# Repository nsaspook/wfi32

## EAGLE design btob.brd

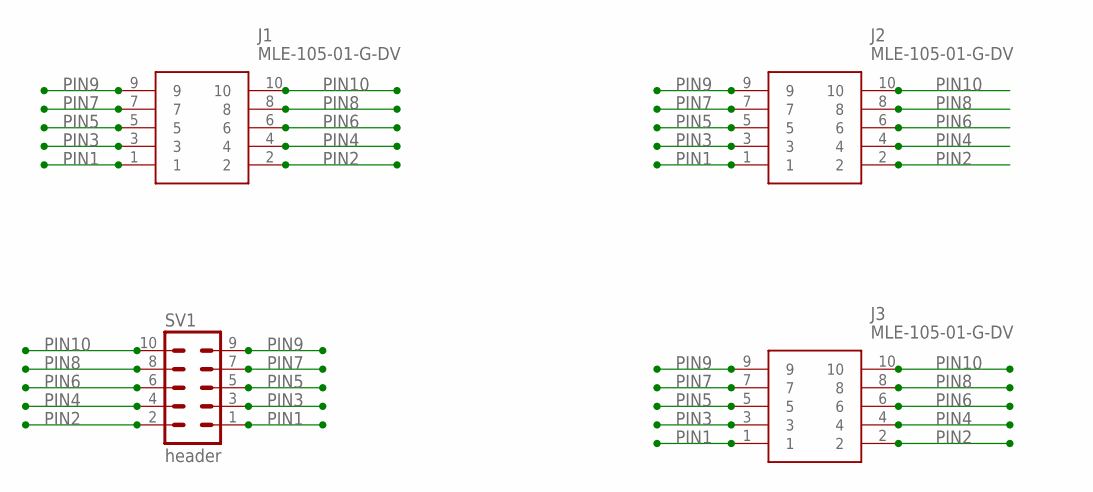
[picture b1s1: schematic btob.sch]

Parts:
J1, J2, J3: MLE-105-01-G-DV
SV1: header; MA05-2

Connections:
PIN1: J1.1, J2.1, J3.1, SV1.1
PIN2: J1.2, J2.2, J3.2, SV1.2
PIN3: J1.3, J2.3, J3.3, SV1.3
PIN4: J1.4, J2.4, J3.4, SV1.4
PIN5: J1.5, J2.5, J3.5, SV1.5
PIN6: J1.6, J2.6, J3.6, SV1.6
PIN7: J1.7, J2.7, J3.7, SV1.7
PIN8: J1.8, J2.8, J3.8, SV1.8
PIN9: J1.9, J2.9, J3.9, SV1.9
PIN10: J1.10, J2.10, J3.10, SV1.10

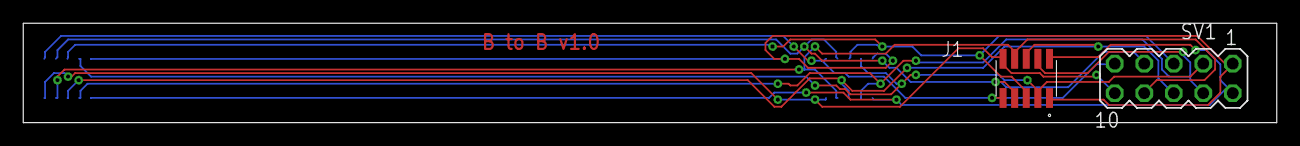
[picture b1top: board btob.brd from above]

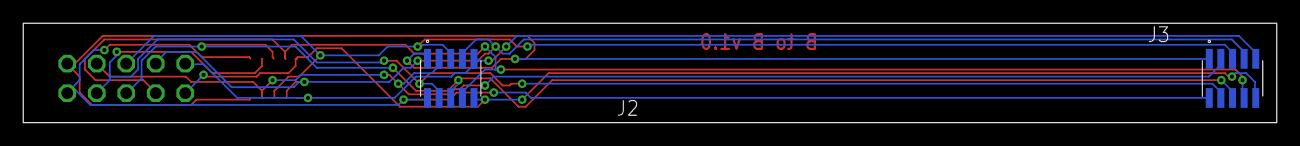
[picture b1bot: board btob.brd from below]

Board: 2 copper layers, 107.9 x 8.6 mm, 4 parts (2 on the bottom side), 10 nets.

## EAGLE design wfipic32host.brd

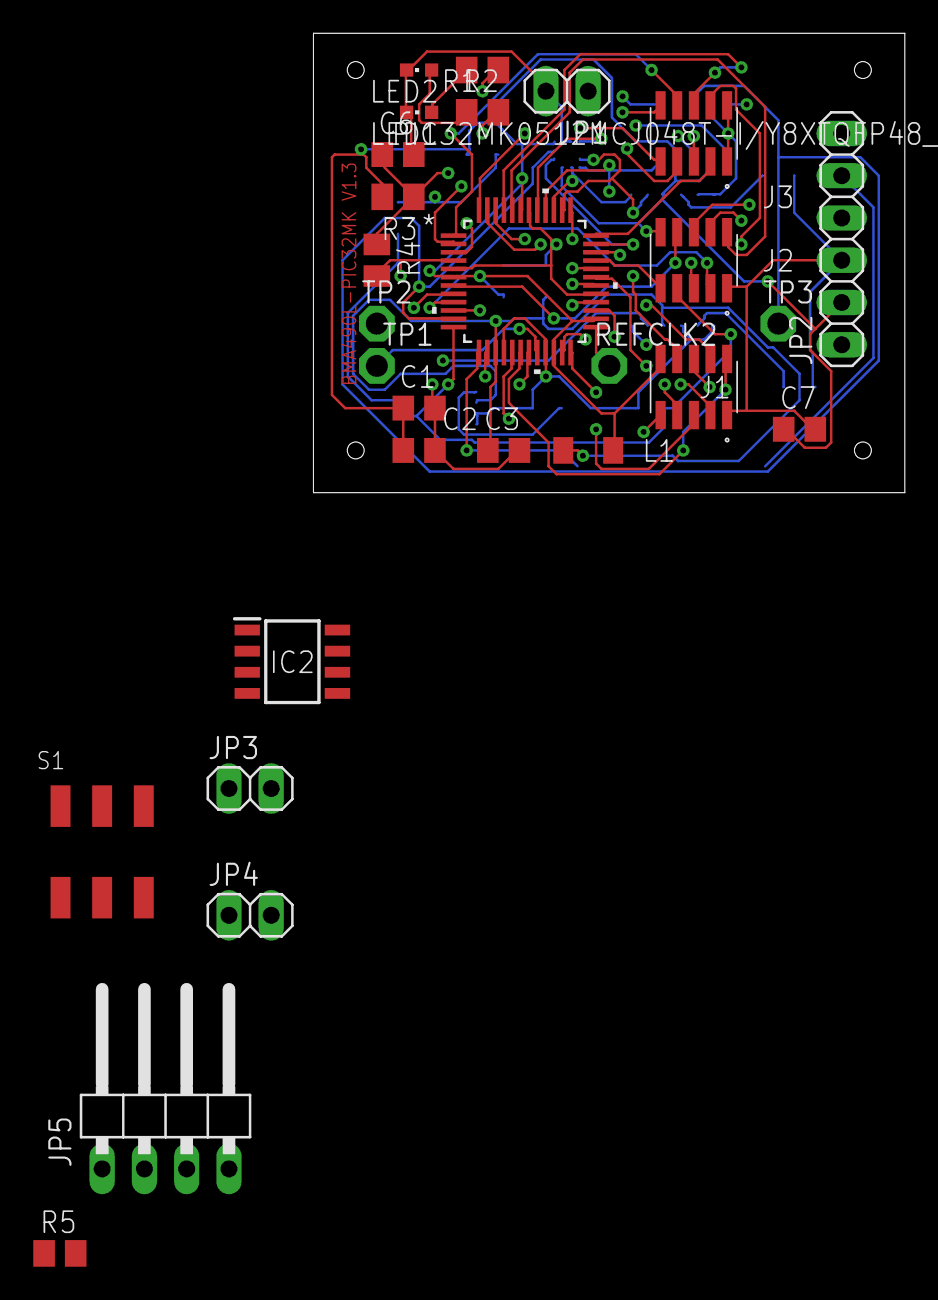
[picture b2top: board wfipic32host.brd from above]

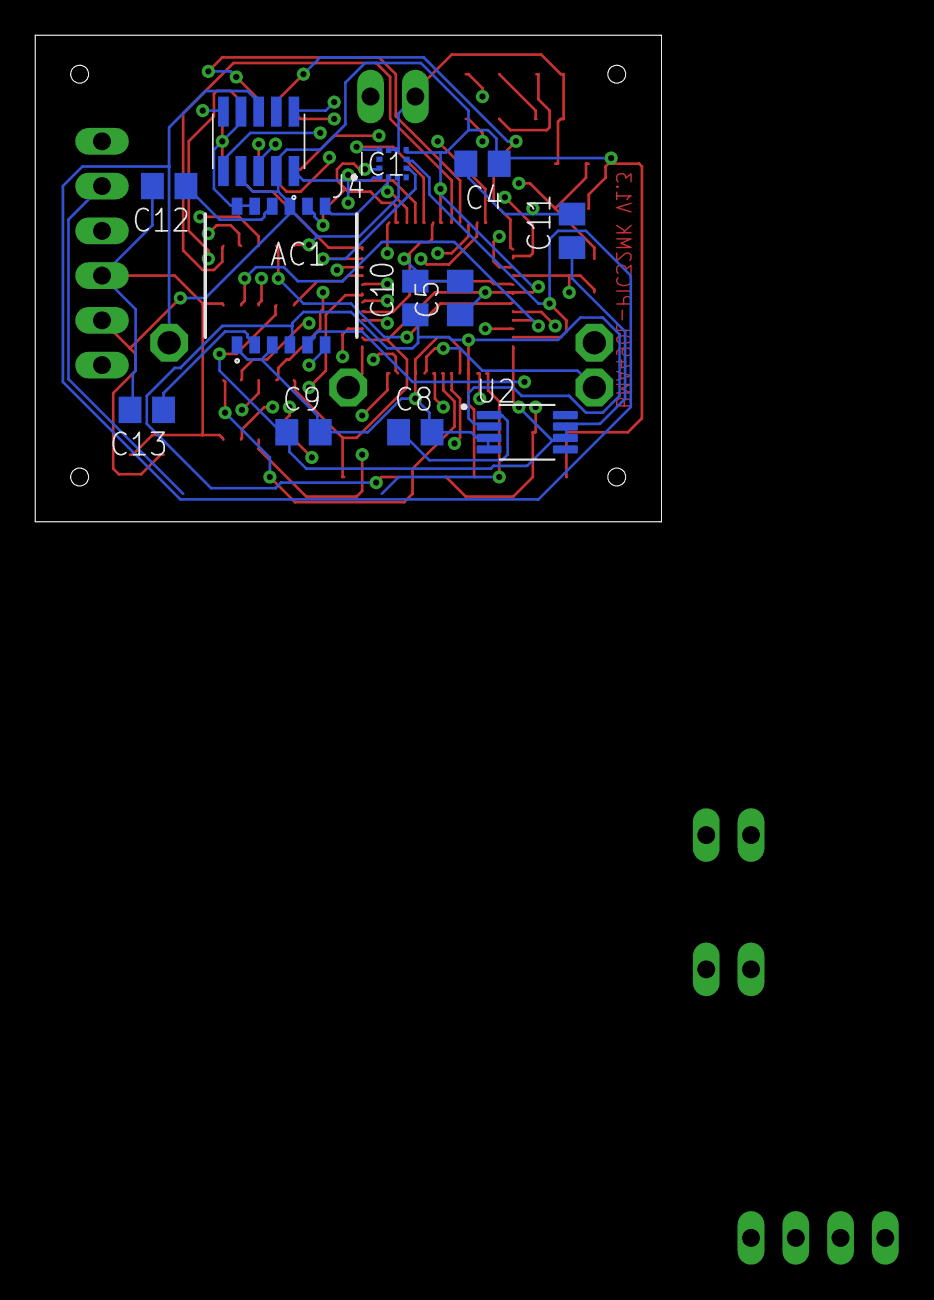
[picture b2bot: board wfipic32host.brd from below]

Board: 4 copper layers, 35.5 x 27.6 mm, 40 parts (12 on the bottom side), 53 nets.

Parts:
AC1: SCA3300-D01-1; SCA3300
C1, C3, C4, C5, C6, C8, C9, C10: 0.1uf; C0805
C2, C7, C11: 10uf; C0805
C12, C13: 0.01uf; C0805
IC1: BMA490L
IC2: TCAN330GD; SOIC127P600X175-8N
J1, J2, J3, J4: MLE-105-01-G-DV
JP1, JP3, JP4: RESET_JMP; 1X02
JP2: ICSP; 1X06
JP5: CAN-FD; 1X04/90
L1: 100uh; L3216C
LED1: RED; CHIPLED_0603
LED2: GREEN; CHIPLED_0603
R1, R2: 2k; M0805
R3: 10k; M0805
R4: 56; M0805
R5: 120; M0805
REFCLK2: PTR1PAD1-13; P1-13
S1: JS202011SCQN; SW_JS202011SCQN
TP1, TP2, TP3: PTR1PAD1-13; P1-13
U1: PIC32MK0512MCJ048T-I/Y8XTQFP48_Y8X_MCH-M; TQFP48_Y8X_MCH-M
U2: MAX6126B30; SOP65P490X110-8N

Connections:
AN0: J2.3, U1.9
AN1: J2.5, U1.10
AVDD: AC1.4, C3.1, C10.1, L1.1, U1.15, U2.2
BMA_INT2: IC1.6, J4.6, TP3.TP, U1.11
CANH: IC2.7, JP5.3, R5.2
CANL: IC2.6, JP5.1, R5.1
DAC1: J2.9, U1.33
EXT_INT2: IC1.5, J4.5, U1.35
EXT_SW1: J1.6, U1.8
EXT_SW2: J2.8, U1.7
GREEN_LED: R2.2, U1.27
IMU_CS: AC1.5, IC1.10, J4.9, U1.41
INDX2: J2.6, U1.46
MCLR_SIG: JP2.1, R4.2, U1.4
unnamed: LED1.A, R1.1
unnamed: LED2.A, R2.1
unnamed: C6.1, JP1.1, R3.1, R4.1
unnamed: C8.1, U2.1
unnamed: TP1.TP, U1.20
unnamed: TP2.TP, U1.19
unnamed: AC1.10, C12.1
unnamed: REFCLK2.TP, U1.25
unnamed: AC1.2, C13.1
unnamed: IC2.1, S1.6
unnamed: IC2.4, S1.3
unnamed: IC2.5, JP4.2
unnamed: IC2.8, JP3.2
PGC_C1RX: JP2.5, S1.2, U1.13
PGD_C1TX: JP2.4, S1.5, U1.14
PWM1EN: J3.5, U1.30
PWM1ER: J3.3, U1.36
PWM1H: J3.9, U1.2
PWM1L: J3.7, U1.3
PWM4EN: J3.6, U1.45
PWM4ER: J3.4, U1.23
PWM4H: J3.10, U1.48
PWM4L: J3.8, U1.1
QEA2: J2.2, U1.44
QEB2: J2.4, U1.47
RED_LED: R1.2, U1.28
SCK1: J1.8, U1.34
SCK2: AC1.8, IC1.12, J4.10, U1.38
SDI1: J1.5, U1.24
SDI1_MODE: J1.4, U1.37
SDI2: AC1.6, IC1.1, J4.1, U1.40
SDO1: J1.7, U1.31
SDO2: AC1.7, IC1.2, J4.2, U1.39
SS1_OUT: J1.9, U1.32
U1RX: J1.2, U1.18
U1TX: J1.3, U1.17
VDD: AC1.9, C1.1, C2.1, C4.1, C5.1, C7.1, IC1.3, IC1.7, IC2.2, J1.10, J2.10, J4.3, J4.7, JP2.2, JP3.1, JP4.1, JP5.4, L1.2, R3.2, U1.6, U1.22, U1.26, U1.43
VREF+: C9.1, C11.1, J2.7, U1.12, U2.6, U2.7
VSS: AC1.1, AC1.3, AC1.11, AC1.12, C1.2, C2.2, C3.2, C4.2, C5.2, C6.2, C7.2, C8.2, C9.2, C10.2, C11.2, C12.2, C13.2, IC1.8, IC1.9, IC2.3, J1.1, J2.1, J3.1, J3.2, J4.8, JP1.2, JP2.3, JP5.2, LED1.C, LED2.C, U1.5, U1.16, U1.21, U1.29, U1.42, U2.3, U2.4

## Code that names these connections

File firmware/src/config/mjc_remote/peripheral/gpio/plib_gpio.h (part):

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// *****************************************************************************


/*** Macros for EXT_SW2 pin ***/
#define EXT_SW2_Set()               (LATASET = (1U<<12))
#define EXT_SW2_Clear()             (LATACLR = (1U<<12))
#define EXT_SW2_Toggle()            (LATAINV= (1U<<12))
#define EXT_SW2_OutputEnable()      (TRISACLR = (1U<<12))
#define EXT_SW2_InputEnable()       (TRISASET = (1U<<12))
#define EXT_SW2_Get()               ((PORTA >> 12) & 0x1U)
#define EXT_SW2_PIN                  GPIO_PIN_RA12

/*** Macros for EXT_SW1 pin ***/
#define EXT_SW1_Set()               (LATASET = (1U<<11))
#define EXT_SW1_Clear()             (LATACLR = (1U<<11))
#define EXT_SW1_Toggle()            (LATAINV= (1U<<11))
#define EXT_SW1_OutputEnable()      (TRISACLR = (1U<<11))
#define EXT_SW1_InputEnable()       (TRISASET = (1U<<11))
#define EXT_SW1_Get()               ((PORTA >> 11) & 0x1U)
#define EXT_SW1_PIN                  GPIO_PIN_RA11

/*** Macros for TP3 pin ***/
#define TP3_Set()               (LATBSET = (1U<<0))
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#define TP1_Get()               ((PORTC >> 11) & 0x1U)
#define TP1_PIN                  GPIO_PIN_RC11

/*** Macros for PWM4ER pin ***/
#define PWM4ER_Set()               (LATASET = (1U<<8))
#define PWM4ER_Clear()             (LATACLR = (1U<<8))
#define PWM4ER_Toggle()            (LATAINV= (1U<<8))
#define PWM4ER_OutputEnable()      (TRISACLR = (1U<<8))
#define PWM4ER_InputEnable()       (TRISASET = (1U<<8))
#define PWM4ER_Get()               ((PORTA >> 8) & 0x1U)
#define PWM4ER_PIN                  GPIO_PIN_RA8

/*** Macros for LED_GREEN pin ***/
#define LED_GREEN_Set()               (LATASET = (1U<<4))
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#define LED_RED_Get()               ((PORTC >> 15) & 0x1U)
#define LED_RED_PIN                  GPIO_PIN_RC15

/*** Macros for PWM1EN pin ***/
#define PWM1EN_Set()               (LATDSET = (1U<<8))
#define PWM1EN_Clear()             (LATDCLR = (1U<<8))
#define PWM1EN_Toggle()            (LATDINV= (1U<<8))
#define PWM1EN_OutputEnable()      (TRISDCLR = (1U<<8))
#define PWM1EN_InputEnable()       (TRISDSET = (1U<<8))
#define PWM1EN_Get()               ((PORTD >> 8) & 0x1U)
#define PWM1EN_PIN                  GPIO_PIN_RD8

/*** Macros for DIS_CS pin ***/
#define DIS_CS_Set()               (LATBSET = (1U<<6))
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#define DIS_CS_Get()               ((PORTB >> 6) & 0x1U)
#define DIS_CS_PIN                  GPIO_PIN_RB6

/*** Macros for PWM1ER pin ***/
#define PWM1ER_Set()               (LATBSET = (1U<<8))
#define PWM1ER_Clear()             (LATBCLR = (1U<<8))
#define PWM1ER_Toggle()            (LATBINV= (1U<<8))
#define PWM1ER_OutputEnable()      (TRISBCLR = (1U<<8))
#define PWM1ER_InputEnable()       (TRISBSET = (1U<<8))
#define PWM1ER_Get()               ((PORTB >> 8) & 0x1U)
#define PWM1ER_PIN                  GPIO_PIN_RB8

/*** Macros for DIS_MODE pin ***/
#define DIS_MODE_Set()               (LATBSET = (1U<<9))
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#define DIS_MODE_Get()               ((PORTB >> 9) & 0x1U)
#define DIS_MODE_PIN                  GPIO_PIN_RB9

/*** Macros for IMU_CS pin ***/
#define IMU_CS_Set()               (LATCSET = (1U<<9))
#define IMU_CS_Clear()             (LATCCLR = (1U<<9))
#define IMU_CS_Toggle()            (LATCINV= (1U<<9))
#define IMU_CS_OutputEnable()      (TRISCCLR = (1U<<9))
#define IMU_CS_InputEnable()       (TRISCSET = (1U<<9))
#define IMU_CS_Get()               ((PORTC >> 9) & 0x1U)
#define IMU_CS_PIN                  GPIO_PIN_RC9

/*** Macros for PWM4EN pin ***/
#define PWM4EN_Set()               (LATBSET = (1U<<11))
#define PWM4EN_Clear()             (LATBCLR = (1U<<11))
#define PWM4EN_Toggle()            (LATBINV= (1U<<11))
#define PWM4EN_OutputEnable()      (TRISBCLR = (1U<<11))
#define PWM4EN_InputEnable()       (TRISBSET = (1U<<11))
#define PWM4EN_Get()               ((PORTB >> 11) & 0x1U)
#define PWM4EN_PIN                  GPIO_PIN_RB11


// *****************************************************************************
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
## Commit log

2023-01-25 1.6 update
2023-02-01 work on uart flow control
2023-02-01 update PCB design
2023-02-25 fix sprintf to snprintf
2023-11-06 mqtt functions
2023-11-06 up mqtt sort of working
2025-04-16 restart MQTT source configuration
2026-05-11 rework for small sensor board with SCL imu chip

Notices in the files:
firmware/src/config/mjc_remote/peripheral/gpio/plib_gpio.h:
Copyright (C) 2019 Microchip Technology Inc. and its subsidiaries.
parts and their libraries:
COPYRIGHT: Copyright (C) 2022 Ultra Librarian. All rights reserved.
